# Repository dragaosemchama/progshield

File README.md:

# progshield
A arduino shield for programming ATmegas

## Usage

This uses default pins in Arduino as ISP example.  Just use your favorite way of etching and load the example into your Arduino. This is a single face board and should be easy to make at home.

## Board preview

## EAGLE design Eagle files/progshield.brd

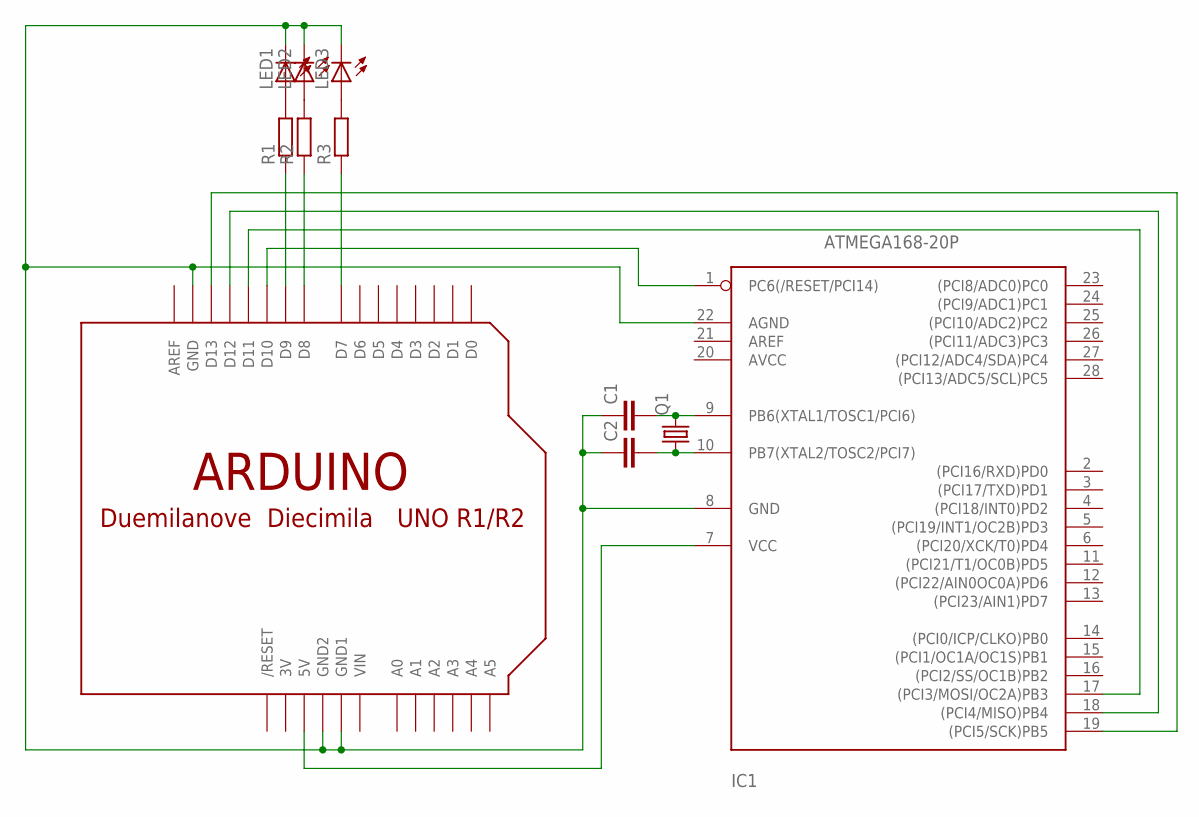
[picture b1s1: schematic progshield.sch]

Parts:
C1, C2: C-EU025-030X050; C025-030X050
IC1: ATMEGA168-20P; DIL28-3
LED1, LED2, LED3: LED3MM
Q1: CRYSTALHC49S; HC49/S
R1, R2, R3: R-EU_0204/7; 0204/7
U$1: ARDUINOUNO; ARDUINO

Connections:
3V: U$1.3V
unnamed: IC1.7 (VCC), U$1.5V
unnamed: IC1.1 (PC6(/RESET/PCI14)), U$1.D10
unnamed: C1.2, IC1.9 (PB6(XTAL1/TOSC1/PCI6)), Q1.2
unnamed: C2.2, IC1.10 (PB7(XTAL2/TOSC2/PCI7)), Q1.1
unnamed: IC1.19 ((PCI5/SCK)PB5), U$1.D13
unnamed: IC1.18 ((PCI4/MISO)PB4), U$1.D12
unnamed: IC1.17 ((PCI3/MOSI/OC2A)PB3), U$1.D11
unnamed: R1.1, U$1.D9
unnamed: R2.1, U$1.D8
unnamed: R3.1, U$1.D7
unnamed: LED3.A, R3.2
unnamed: LED2.A, R2.2
unnamed: LED1.A, R1.2
unnamed: C1.1, C2.1, IC1.8 (GND), IC1.22 (AGND), LED1.K (C), LED2.K (C), LED3.K (C), U$1.GND, U$1.GND1, U$1.GND2
VIN: U$1.VIN

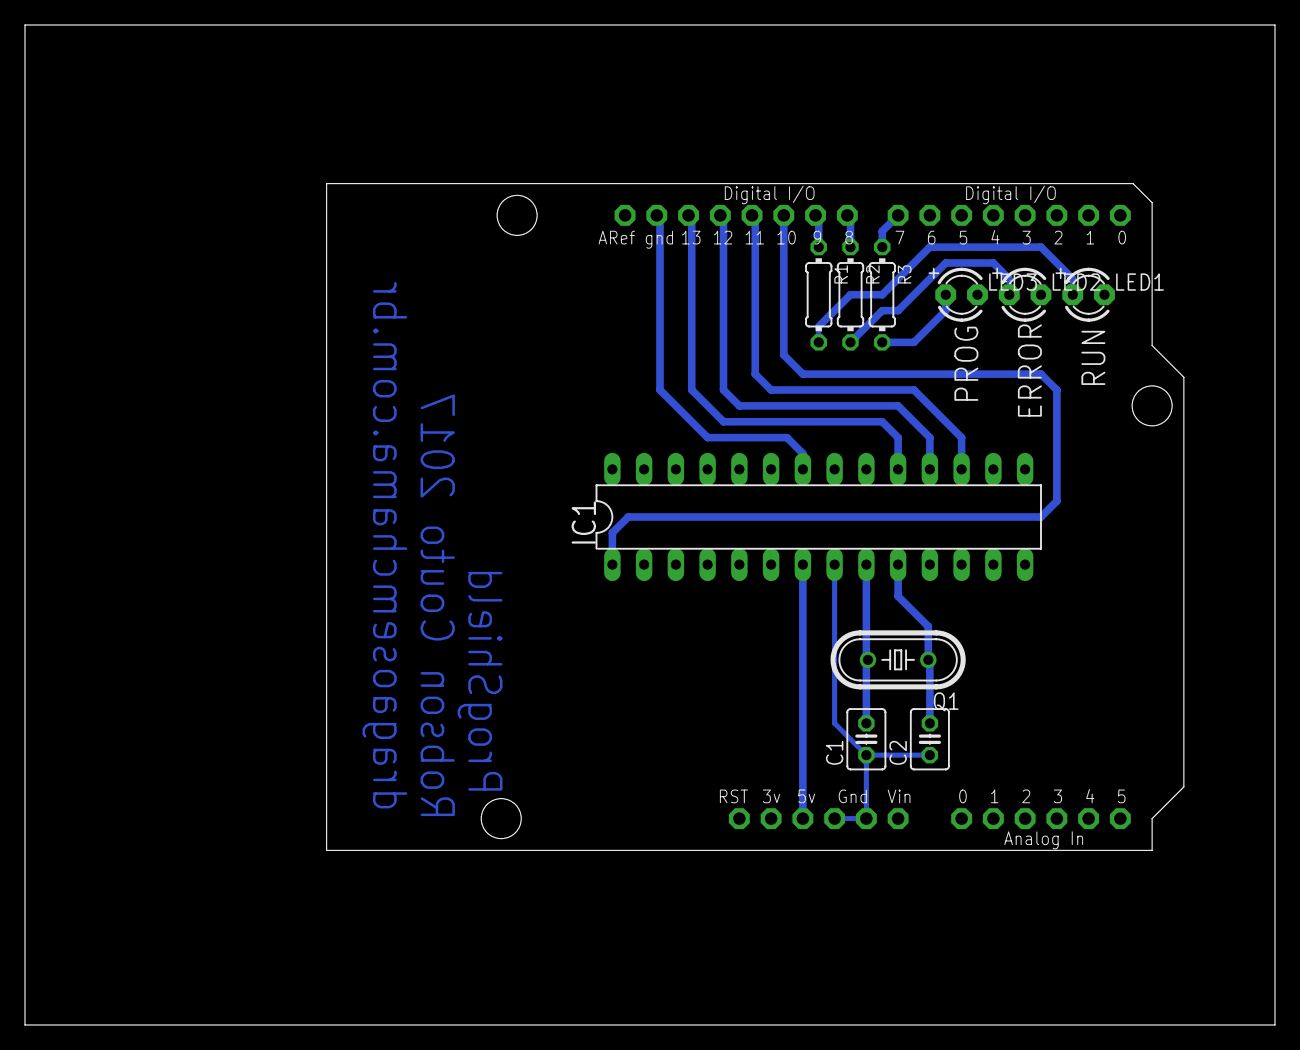
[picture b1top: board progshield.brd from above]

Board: 2 copper layers, 100.0 x 80.0 mm, 11 parts (0 on the bottom side), 14 nets.

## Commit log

2017-04-29 Added files to repo
    Added ealge project files and a pdf for the board layout
2017-04-29 Moved eagle files to a folder
    Added a picture of the project
